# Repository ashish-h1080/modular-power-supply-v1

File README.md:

# ModuloVolt (V1.02) - modular power supply 
This modular power supply circuit provides selectable fixed and adjustable voltage outputs using LM2596 regulators. It integrates a 555 timer-based pulse generator and supports multiple operational modes via switchable configurations. The design includes high-side switching for improved isolation and safety.

## Features
This modular power supply system offers a range of features designed for flexibility and reliability. It provides switchable voltage outputs, including a fixed 5V regulated supply using the LM2596-5V and an adjustable output of up to 12V via the LM2596-ADJ, controlled by a potentiometer. To ensure proper isolation and seamless switching between these voltage sources, a high-side DPDT switch is integrated into the design. Additionally, the system includes an integrated pulse generator, utilizing a 555 timer circuit to produce clock pulses. The pulse frequency can be adjusted by selecting different capacitors, making the system adaptable for various applications requiring precise timing signals.

## Implementation
The modular power supply system is designed for versatility and stability, incorporating key components for power input, regulation, filtering, and additional functionalities. A DC power jack (J1) serves as the main input source, while a DPDT switch (SW2) allows seamless selection between a fixed and an adjustable voltage regulator. The LM2596-5V (U1) ensures a stable 5V output, whereas the LM2596-ADJ (U2), controlled via a 10k potentiometer (RV1), provides a user-defined adjustable voltage. To enhance performance, capacitors (C1-C8) and inductors (L1, L2) are implemented for stability and noise reduction, while Schottky diodes (D1, D2) safeguard the system against reverse voltage. Additionally, a 555 timer (U3) functions as a pulse generator, with its frequency adjustable through capacitors (TC1-TC4) and resistors (RT1, RT2). The generated clock pulses are accessible via a single-pin connector (J3), offering expanded utility for various applications. Finally, a 4 pin terminal block (J2) efficiently distributes power and ground, ensuring easy connectivity for external circuits.

## Future Iterations
- **Onboard volt meter**
- **Additional signal processing (e.g., sine wave generator, filters, amplifiers)**
- **Microcontroller-based control for automated switching and monitoring**

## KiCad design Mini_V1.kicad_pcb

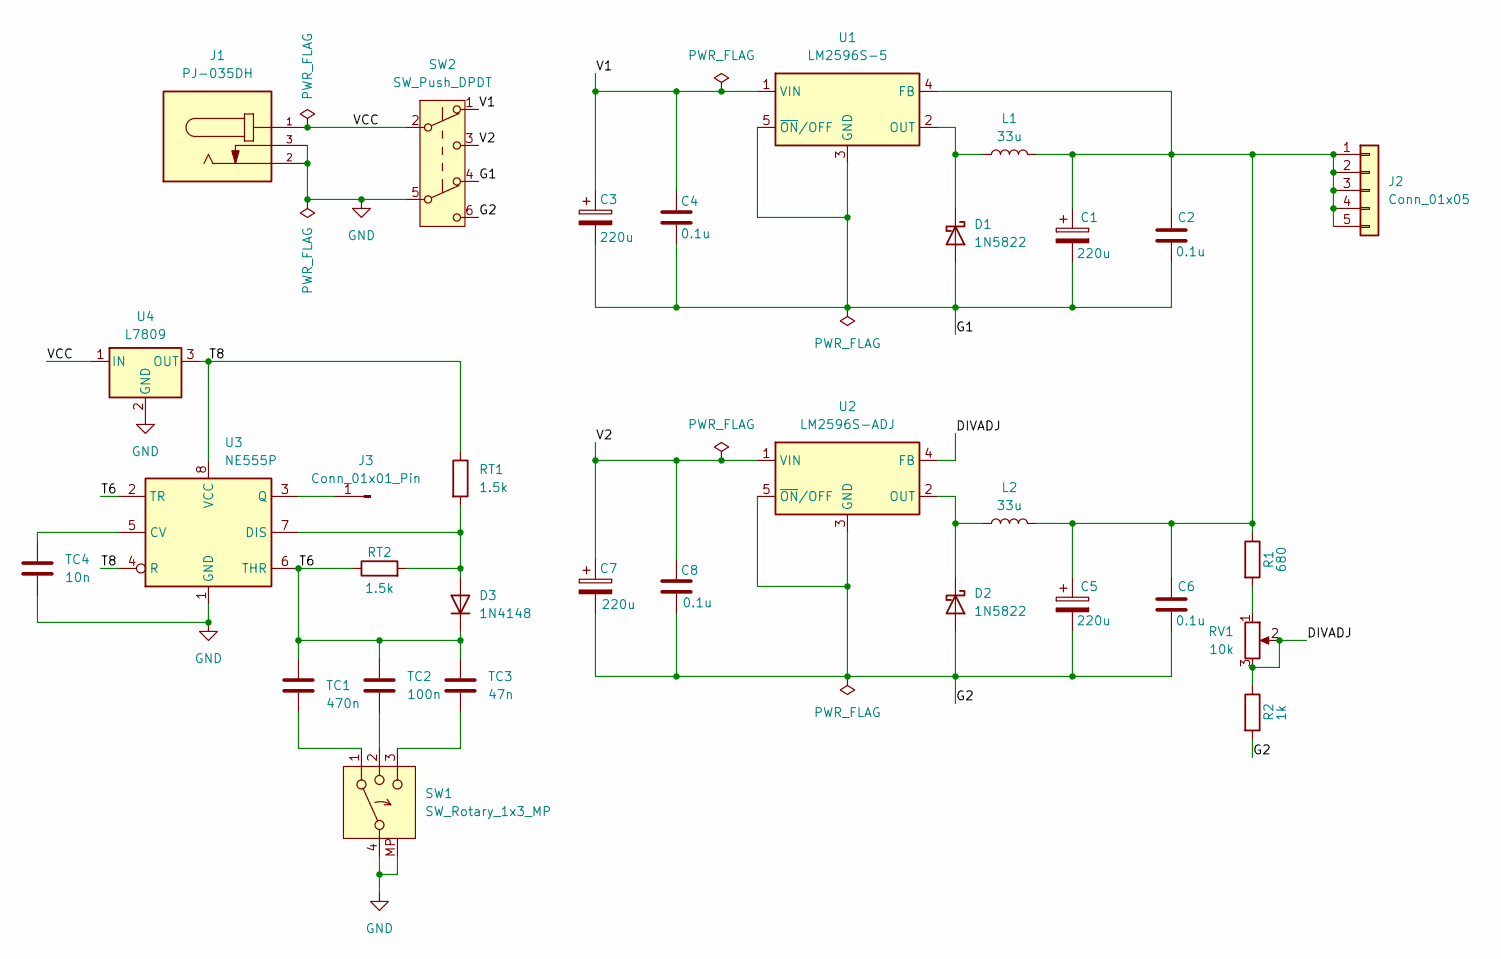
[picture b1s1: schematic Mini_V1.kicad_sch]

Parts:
C1, C3, C5, C7: 220u; CP_Radial_D8.0mm_P3.50mm
C2, C4, C6, C8: 0.1u; C_0805_2012Metric_Pad1.18x1.45mm_HandSolder
D1, D2: 1N5822; D_DO-201AD_P12.70mm_Horizontal
D3: 1N4148; D_DO-35_SOD27_P7.62mm_Horizontal
J1: PJ-035DH; CUI_PJ-035DH; PARTREV 1.05
J2: Conn_01x05; PinHeader_1x05_P2.00mm_Vertical
J3: Conn_01x01_Pin; PinHeader_1x01_P2.00mm_Vertical
L1, L2: 33u; INDP125125X600N
R1: 680; R_Axial_DIN0309_L9.0mm_D3.2mm_P12.70mm_Horizontal
R2: 1k; R_Axial_DIN0309_L9.0mm_D3.2mm_P12.70mm_Horizontal
RT1, RT2: 1.5k; R_0805_2012Metric_Pad1.20x1.40mm_HandSolder
RV1: 10k; Potentiometer_Piher_PC-16_Single_Horizontal
SW1: SW_Rotary_1x3_MP; RotaryEncoder_Bourns_Vertical_PEC12R-3x17F-Nxxxx(custom)
SW2: SW_Push_DPDT; SW_TL2230OAF140
TC1: 470n; C_0805_2012Metric_Pad1.18x1.45mm_HandSolder
TC2: 100n; C_0805_2012Metric_Pad1.18x1.45mm_HandSolder
TC3: 47n; C_0805_2012Metric_Pad1.18x1.45mm_HandSolder
TC4: 10n; C_0805_2012Metric_Pad1.18x1.45mm_HandSolder
U1: LM2596S-5; TO-263-5_TabPin3
U2: LM2596S-ADJ; TO-263-5_TabPin3
U3: NE555P; DIP-8_W7.62mm
U4: L7809; TO-220-3_Horizontal_TabDown

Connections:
/DIVADJ: R2.1, RV1.2, RV1.3, U2.4 (FB)
/G1: C1.2, C2.2, C3.2, C4.2, D1.2 (A), SW2.4 (A), U1.3 (GND), U1.5 (~ON/OFF)
/G2: C5.2, C6.2, C7.2, C8.2, D2.2 (A), R2.2, SW2.6 (C), U2.3 (GND), U2.5 (~ON/OFF)
/T6: D3.1 (K), RT2.1, TC1.1, TC2.1, TC3.1, U3.2 (TR), U3.6 (THR)
/T8: RT1.1, U3.4 (R), U3.8 (VCC), U4.3 (OUT)
/V1: C3.1, C4.1, SW2.1 (A), U1.1 (VIN)
/V2: C7.1, C8.1, SW2.3 (C), U2.1 (VIN)
/VCC: J1.1, SW2.2 (B), U4.1 (IN)
GND: J1.2, J1.3, SW1.4, SW1.MP, SW2.5 (B), TC4.2, U3.1 (GND), U4.2 (GND)
unnamed: D1.1 (K), L1.1, U1.2 (OUT)
unnamed: D2.1 (K), L2.1, U2.2 (OUT)
unnamed: D3.2 (A), RT1.2, RT2.2, U3.7 (DIS)
unnamed: C1.1, C2.1, C5.1, C6.1, J2.1, J2.2, J2.3, J2.4, J2.5, L1.2, L2.2, R1.1, U1.4 (FB)
unnamed: J3.1, U3.3 (Q)
unnamed: R1.2, RV1.1
unnamed: SW1.1, TC1.2
unnamed: SW1.2, TC2.2
unnamed: SW1.3, TC3.2
unnamed: TC4.1, U3.5 (CV)

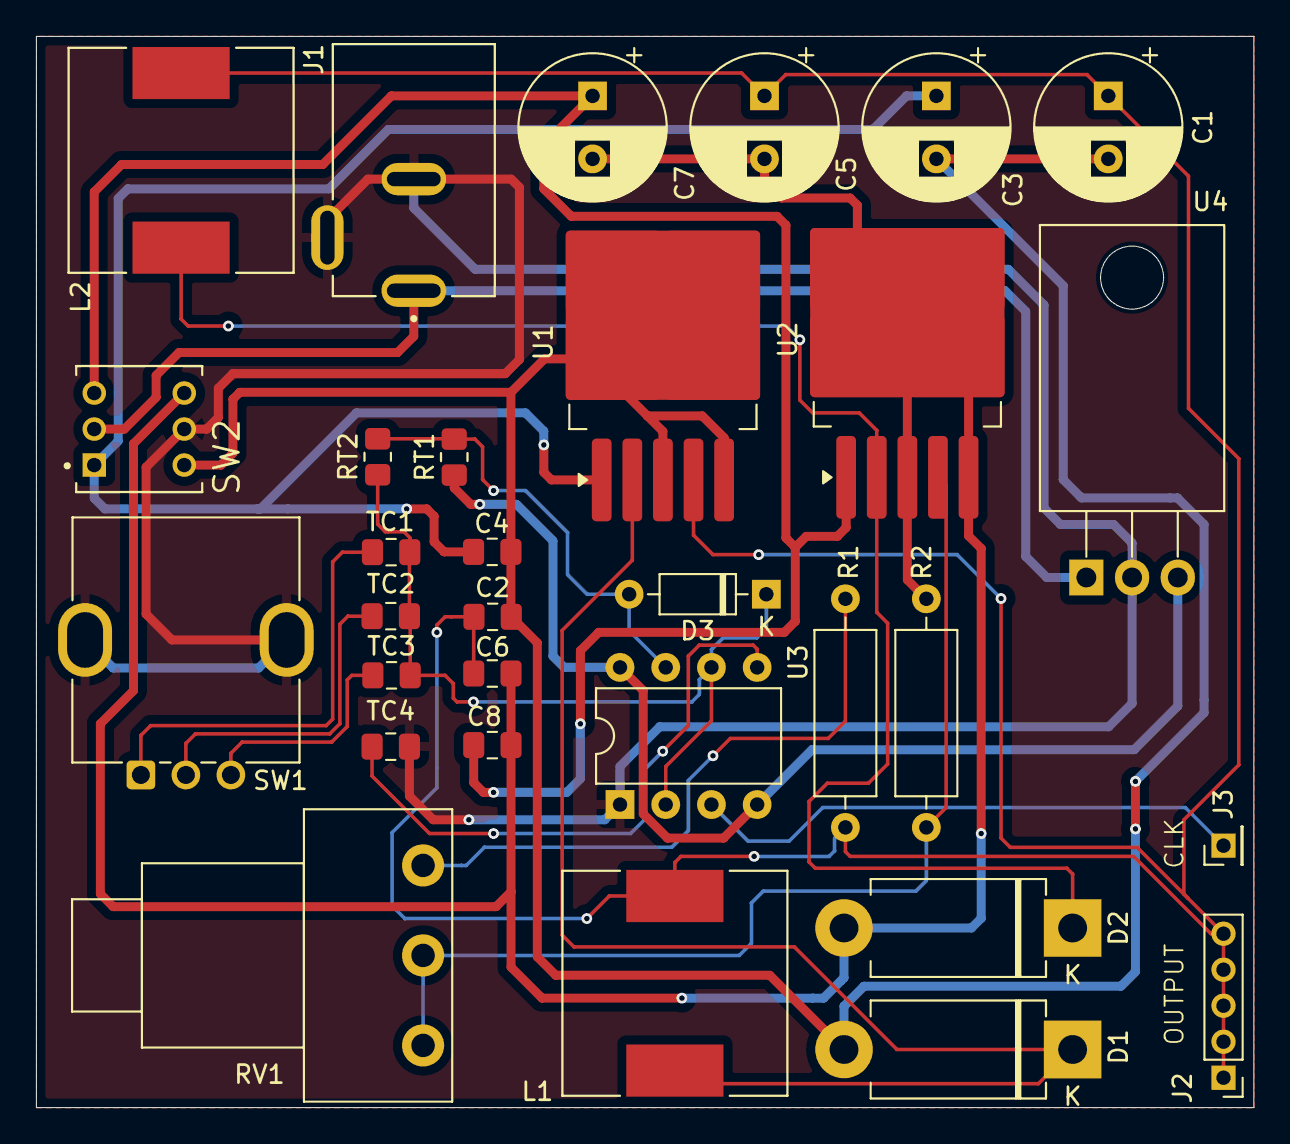
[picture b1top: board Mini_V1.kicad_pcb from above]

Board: 2 copper layers, 67.6 x 59.5 mm, 31 parts (0 on the bottom side), 19 nets.
